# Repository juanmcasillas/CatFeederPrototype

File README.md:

# CatFeeder
Automatic pet feeder, with artificial vision detection, rule based. Managed from a Web Server. Fully automated.

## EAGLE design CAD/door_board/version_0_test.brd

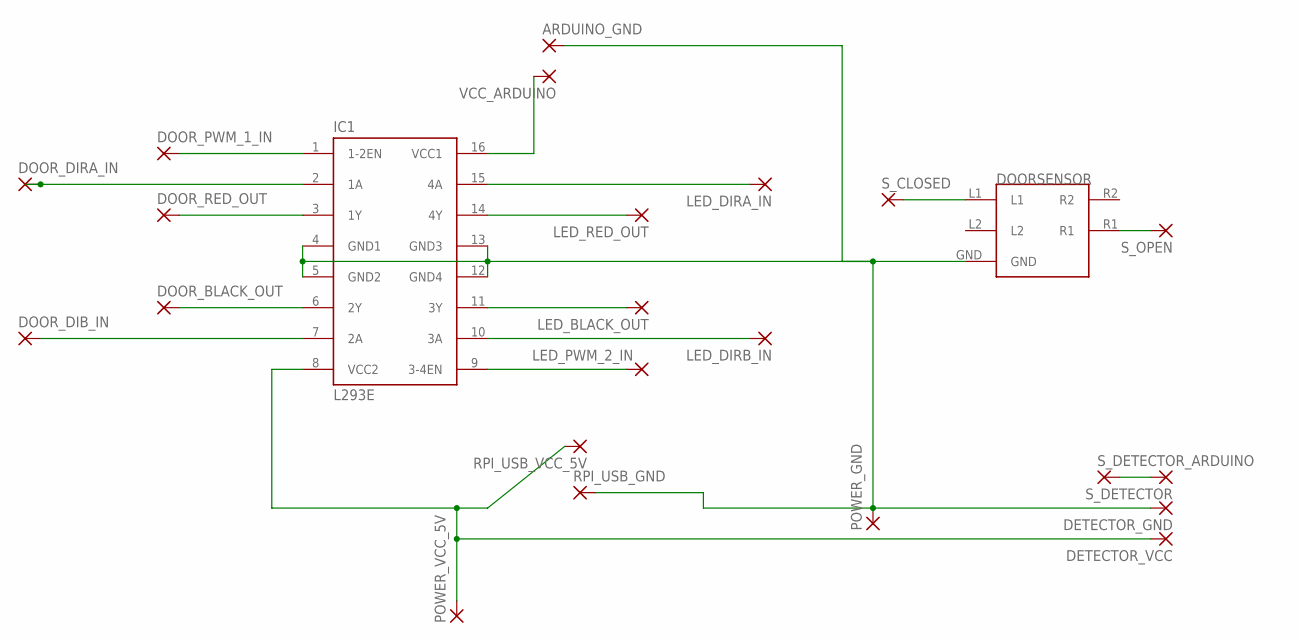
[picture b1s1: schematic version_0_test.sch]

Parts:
ARDUINO_GND: SMD5; SMD2,54-5,08
DETECTOR_GND: SMD5; SMD2,54-5,08
DETECTOR_VCC: SMD5; SMD2,54-5,08
DOORSENSOR: DOORSENSOR
DOOR_BLACK_OUT: SMD5; SMD2,54-5,08
DOOR_DIB_IN: SMD5; SMD2,54-5,08
DOOR_DIRA_IN: SMD5; SMD2,54-5,08
DOOR_PWM_1_IN: SMD5; SMD2,54-5,08
DOOR_RED_OUT: SMD5; SMD2,54-5,08
IC1: L293E; DIL16
LED_BLACK_OUT: SMD5; SMD2,54-5,08
LED_DIRA_IN: SMD5; SMD2,54-5,08
LED_DIRB_IN: SMD5; SMD2,54-5,08
LED_PWM_2_IN: SMD5; SMD2,54-5,08
LED_RED_OUT: SMD5; SMD2,54-5,08
POWER_GND: SMD5; SMD2,54-5,08
POWER_VCC_5V: SMD5; SMD2,54-5,08
RPI_USB_GND: SMD5; SMD2,54-5,08
RPI_USB_VCC_5V: SMD5; SMD2,54-5,08
S_CLOSED: SMD5; SMD2,54-5,08
S_DETECTOR: SMD5; SMD2,54-5,08
S_DETECTOR_ARDUINO: SMD5; SMD2,54-5,08
S_OPEN: SMD5; SMD2,54-5,08
VCC_ARDUINO: SMD5; SMD2,54-5,08

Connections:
GND: ARDUINO_GND.1, DETECTOR_GND.1, DOORSENSOR.GND, IC1.4 (GND1), IC1.5 (GND2), IC1.12 (GND4), IC1.13 (GND3), POWER_GND.1, RPI_USB_GND.1
unnamed: S_DETECTOR.1, S_DETECTOR_ARDUINO.1
unnamed: DOORSENSOR.L1, S_CLOSED.1
unnamed: DOORSENSOR.R1, S_OPEN.1
unnamed: DOOR_BLACK_OUT.1, IC1.6 (2Y)
unnamed: DOOR_RED_OUT.1, IC1.3 (1Y)
unnamed: IC1.9 (3-4EN), LED_PWM_2_IN.1
unnamed: DOOR_PWM_1_IN.1, IC1.1 (1-2EN)
unnamed: DOOR_DIRA_IN.1, IC1.2 (1A)
unnamed: DOOR_DIB_IN.1, IC1.7 (2A)
unnamed: IC1.10 (3A), LED_DIRB_IN.1
unnamed: IC1.15 (4A), LED_DIRA_IN.1
unnamed: IC1.11 (3Y), LED_BLACK_OUT.1
unnamed: IC1.14 (4Y), LED_RED_OUT.1
VCC_ARDUINO: IC1.16 (VCC1), VCC_ARDUINO.1
VCC_MOTOR: DETECTOR_VCC.1, IC1.8 (VCC2), POWER_VCC_5V.1, RPI_USB_VCC_5V.1

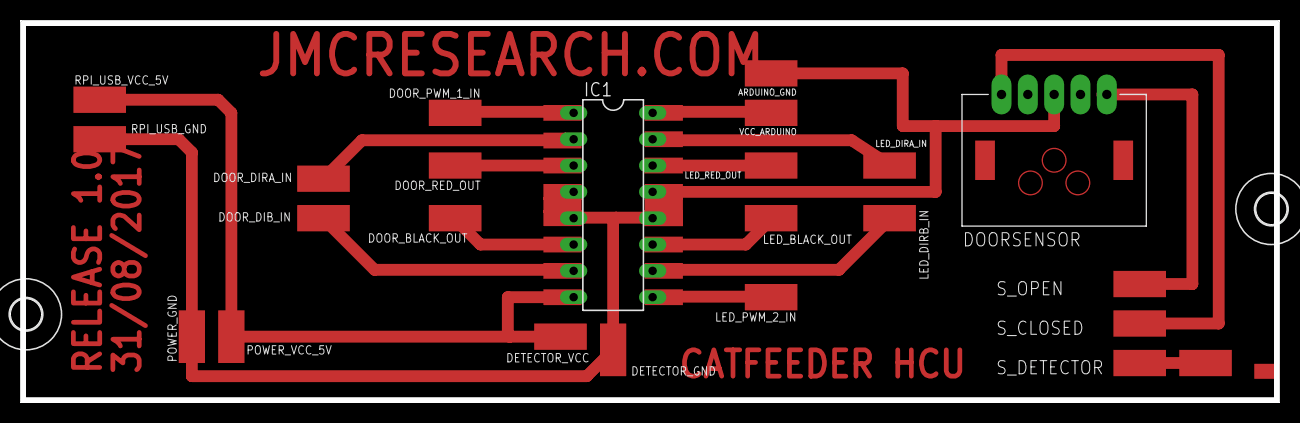
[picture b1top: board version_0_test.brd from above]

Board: 2 copper layers, 120.9 x 36.3 mm, 26 parts (0 on the bottom side), 16 nets.

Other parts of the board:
U$1, U$2: 3,0

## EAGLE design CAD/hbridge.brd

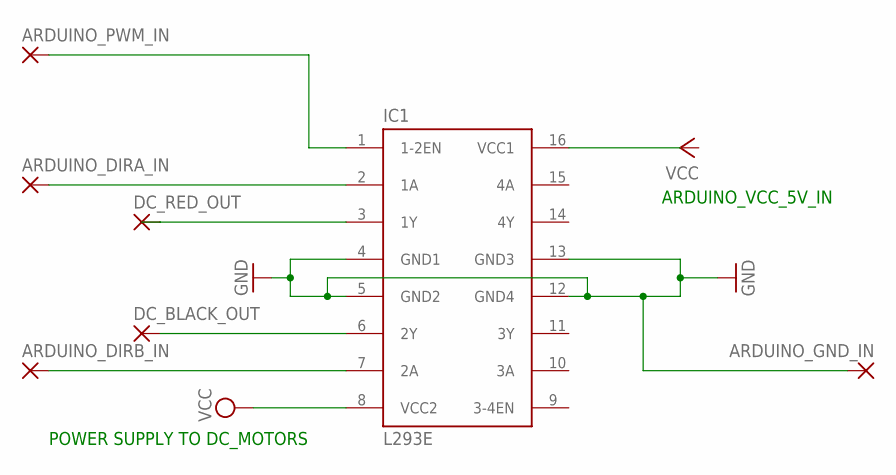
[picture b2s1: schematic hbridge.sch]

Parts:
ARDUINO_DIRA_IN: SMD2; SMD1,27-2,54
ARDUINO_DIRB_IN: SMD2; SMD1,27-2,54
ARDUINO_GND_IN: SMD2; SMD1,27-2,54
ARDUINO_PWM_IN: SMD2; SMD1,27-2,54
DC_BLACK_OUT: SMD2; SMD1,27-2,54
DC_RED_OUT: SMD2; SMD1,27-2,54
IC1: L293E; DIL16

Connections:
GND: ARDUINO_GND_IN.1, IC1.4 (GND1), IC1.5 (GND2), IC1.12 (GND4), IC1.13 (GND3)
unnamed: ARDUINO_PWM_IN.1, IC1.1 (1-2EN)
unnamed: DC_RED_OUT.1, IC1.3 (1Y)
unnamed: DC_BLACK_OUT.1, IC1.6 (2Y)
unnamed: ARDUINO_DIRA_IN.1, IC1.2 (1A)
unnamed: ARDUINO_DIRB_IN.1, IC1.7 (2A)
VCC: IC1.8 (VCC2)

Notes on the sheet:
POWER SUPPLY TO DC_MOTORS
ARDUINO_VCC_5V_IN

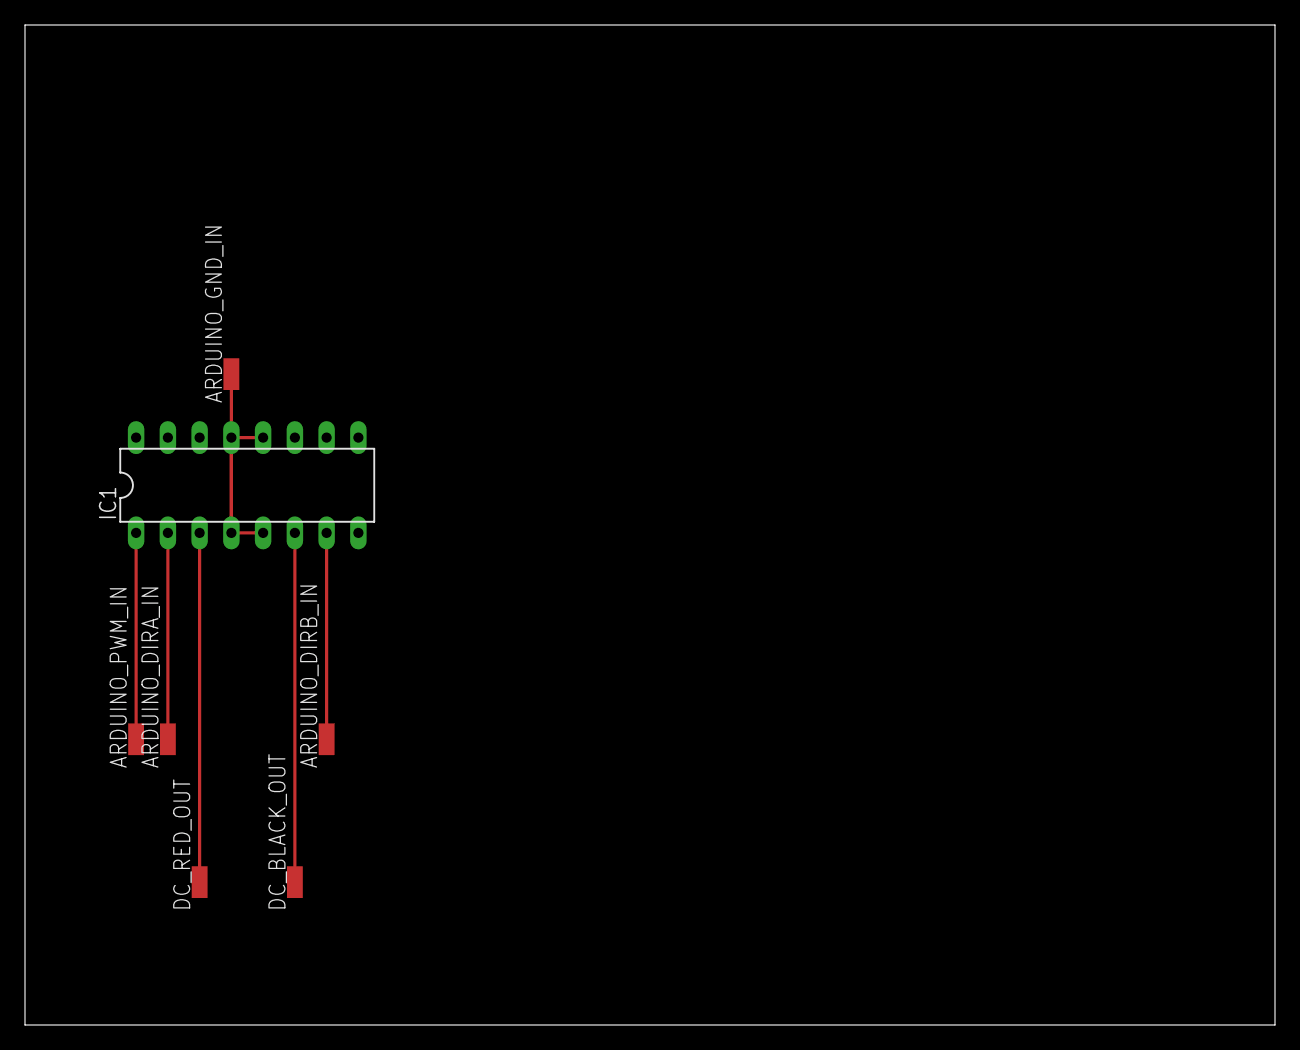
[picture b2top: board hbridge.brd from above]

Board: 2 copper layers, 100.0 x 80.0 mm, 7 parts (0 on the bottom side), 6 nets.

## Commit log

2017-11-01 Initial import
2017-11-01 Added python project files
2017-11-02 Tagged will all the code.
2017-11-02 Deleted dev files.
2017-11-02 Remove all unnecesary files
2017-11-02 Removed the pyc files from python
2017-11-03 Added support for get the default IP (the ip that uses the default interface)
2017-11-03 added gitignore
